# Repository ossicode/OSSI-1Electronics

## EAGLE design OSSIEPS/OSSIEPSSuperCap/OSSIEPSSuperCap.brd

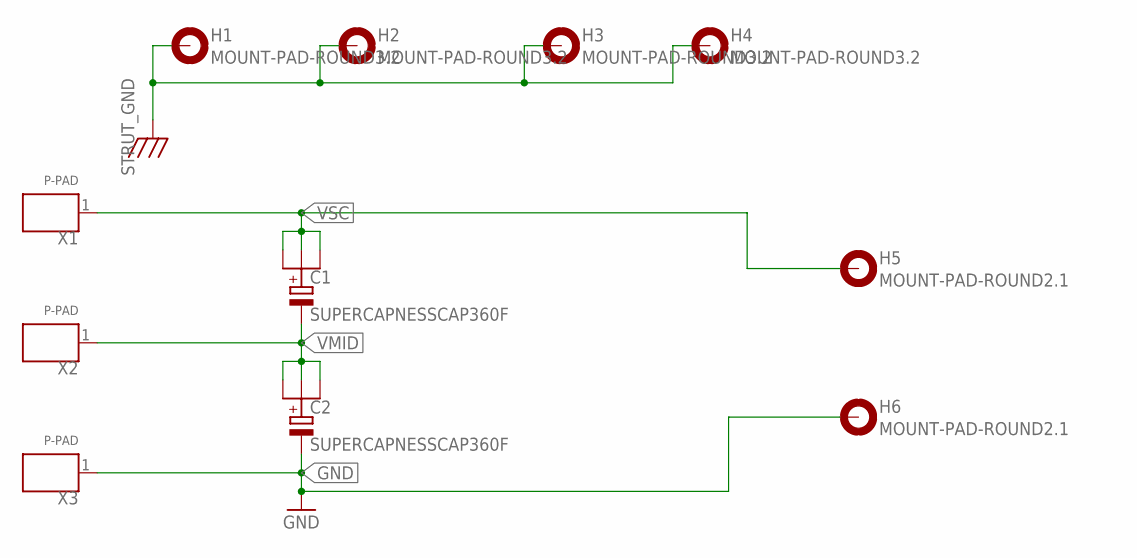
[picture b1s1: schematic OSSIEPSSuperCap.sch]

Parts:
C1, C2: SUPERCAPNESSCAP360F; NESSCAP360F
H1, H2, H3, H4: MOUNT-PAD-ROUND3.2; 3.2-PAD-ROUND
H5, H6: MOUNT-PAD-ROUND2.1; 2.1-PAD-ROUND
X1, X2, X3: P-PAD

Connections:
GND: C2.N, H6.B3,2, X3.1
STRUT_GND: H1.B3,2, H2.B3,2, H3.B3,2, H4.B3,2
VMID: C1.N, C2.P1, C2.P2, C2.P3, X2.1
VSC: C1.P1, C1.P2, C1.P3, H5.B3,2, X1.1

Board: 2 copper layers, 11 parts (0 on the bottom side), 4 nets, no tracks yet.

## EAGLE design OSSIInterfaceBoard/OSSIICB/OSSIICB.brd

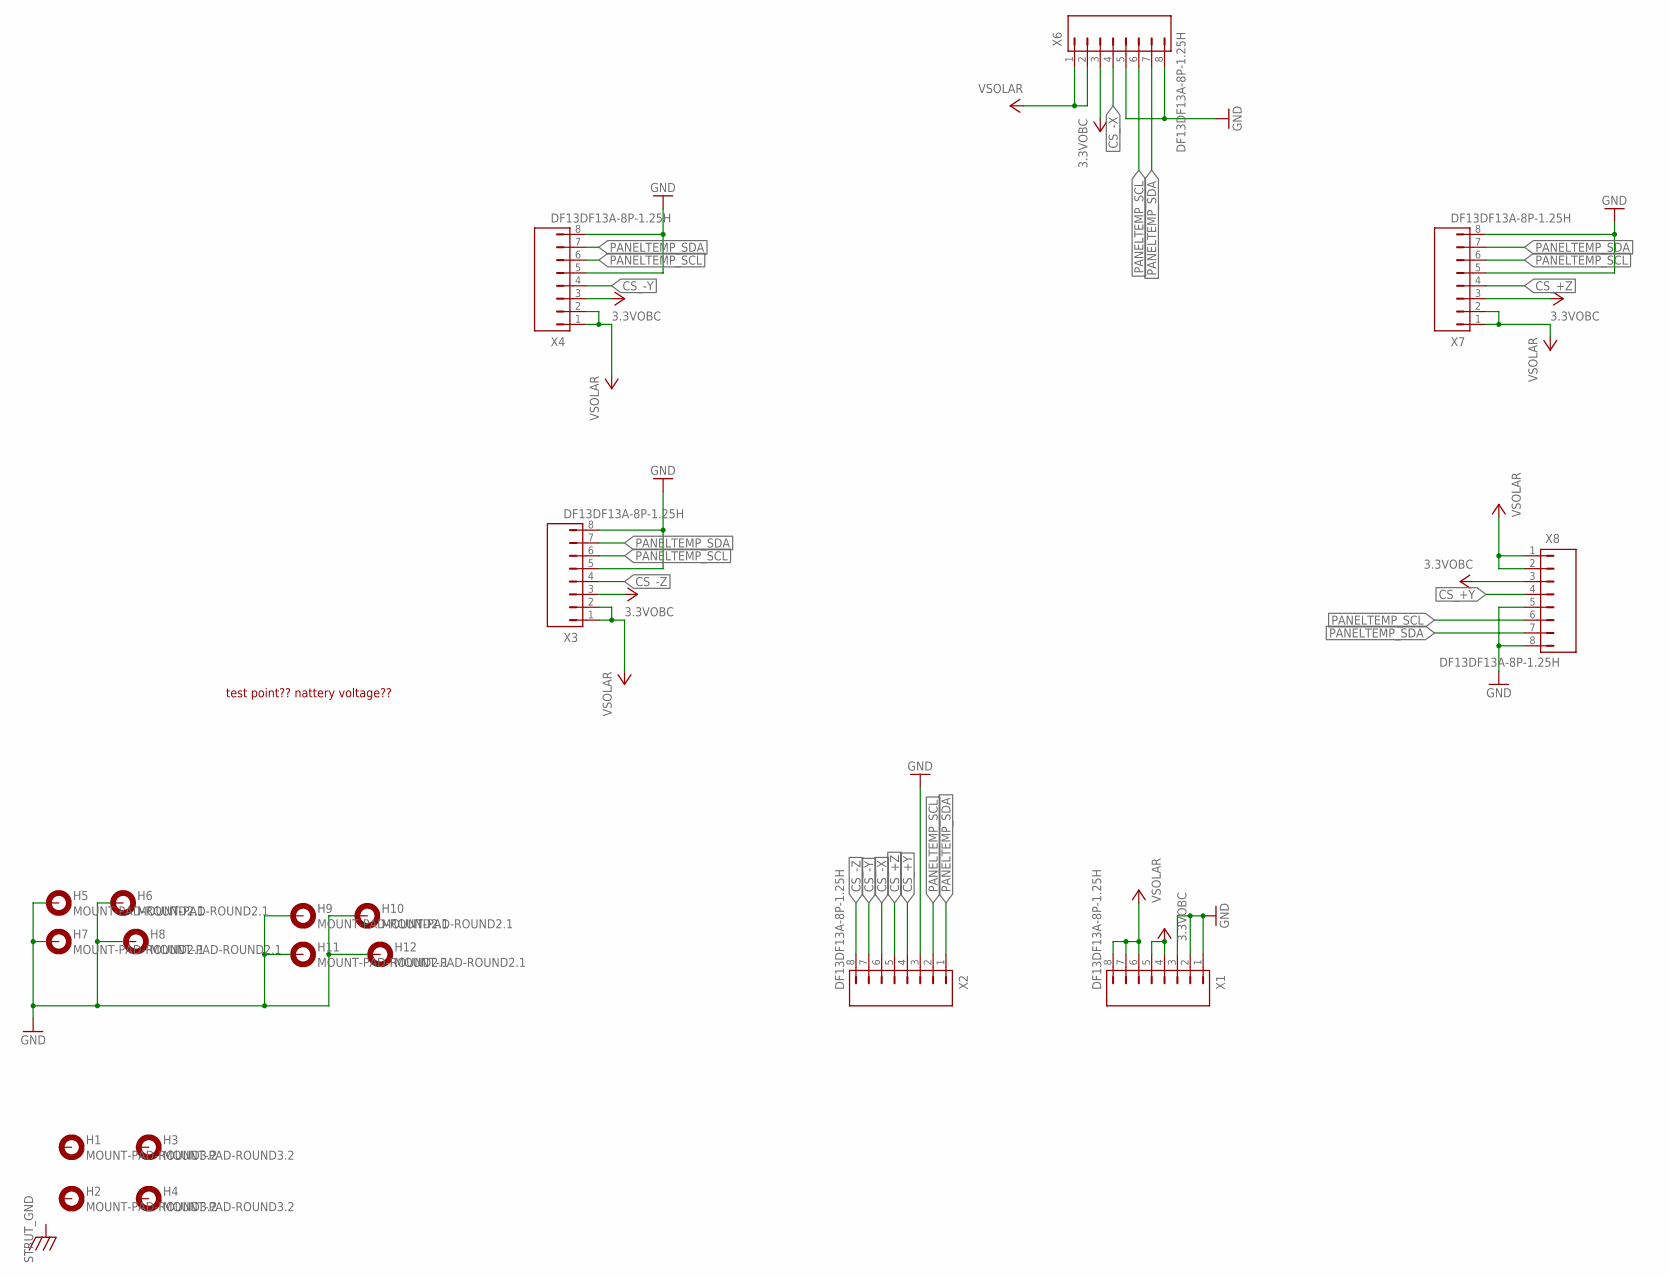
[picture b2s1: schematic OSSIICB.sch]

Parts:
H1, H2, H3, H4: MOUNT-PAD-ROUND3.2; 3.2-PAD-ROUND
H5, H6, H7, H8, H9, H10, H11, H12: MOUNT-PAD-ROUND2.1; 2.1-PAD-ROUND
X1, X2, X3, X4, X6, X7, X8: DF13DF13A-8P-1.25H; DF13A-8P

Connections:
3.3VOBC: X1.4, X1.5, X3.3, X4.3, X6.3, X7.3, X8.3
CS_+Y: X2.4, X8.4
CS_+Z: X2.5, X7.4
CS_-X: X2.6, X6.4
CS_-Y: X2.7, X4.4
CS_-Z: X2.8, X3.4
GND: H5.B3,2, H6.B3,2, H7.B3,2, H8.B3,2, H9.B3,2, H10.B3,2, H11.B3,2, H12.B3,2, X1.1, X1.2, X1.3, X2.3, X3.5, X3.8, X4.5, X4.8, X6.5, X6.8, X7.5, X7.8, X8.5, X8.8
PANELTEMP_SCL: X2.2, X3.6, X4.6, X6.6, X7.6, X8.6
PANELTEMP_SDA: X2.1, X3.7, X4.7, X6.7, X7.7, X8.7
VSOLAR: X1.6, X1.7, X1.8, X3.1, X3.2, X4.1, X4.2, X6.1, X6.2, X7.1, X7.2, X8.1, X8.2

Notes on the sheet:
test point?? nattery voltage??

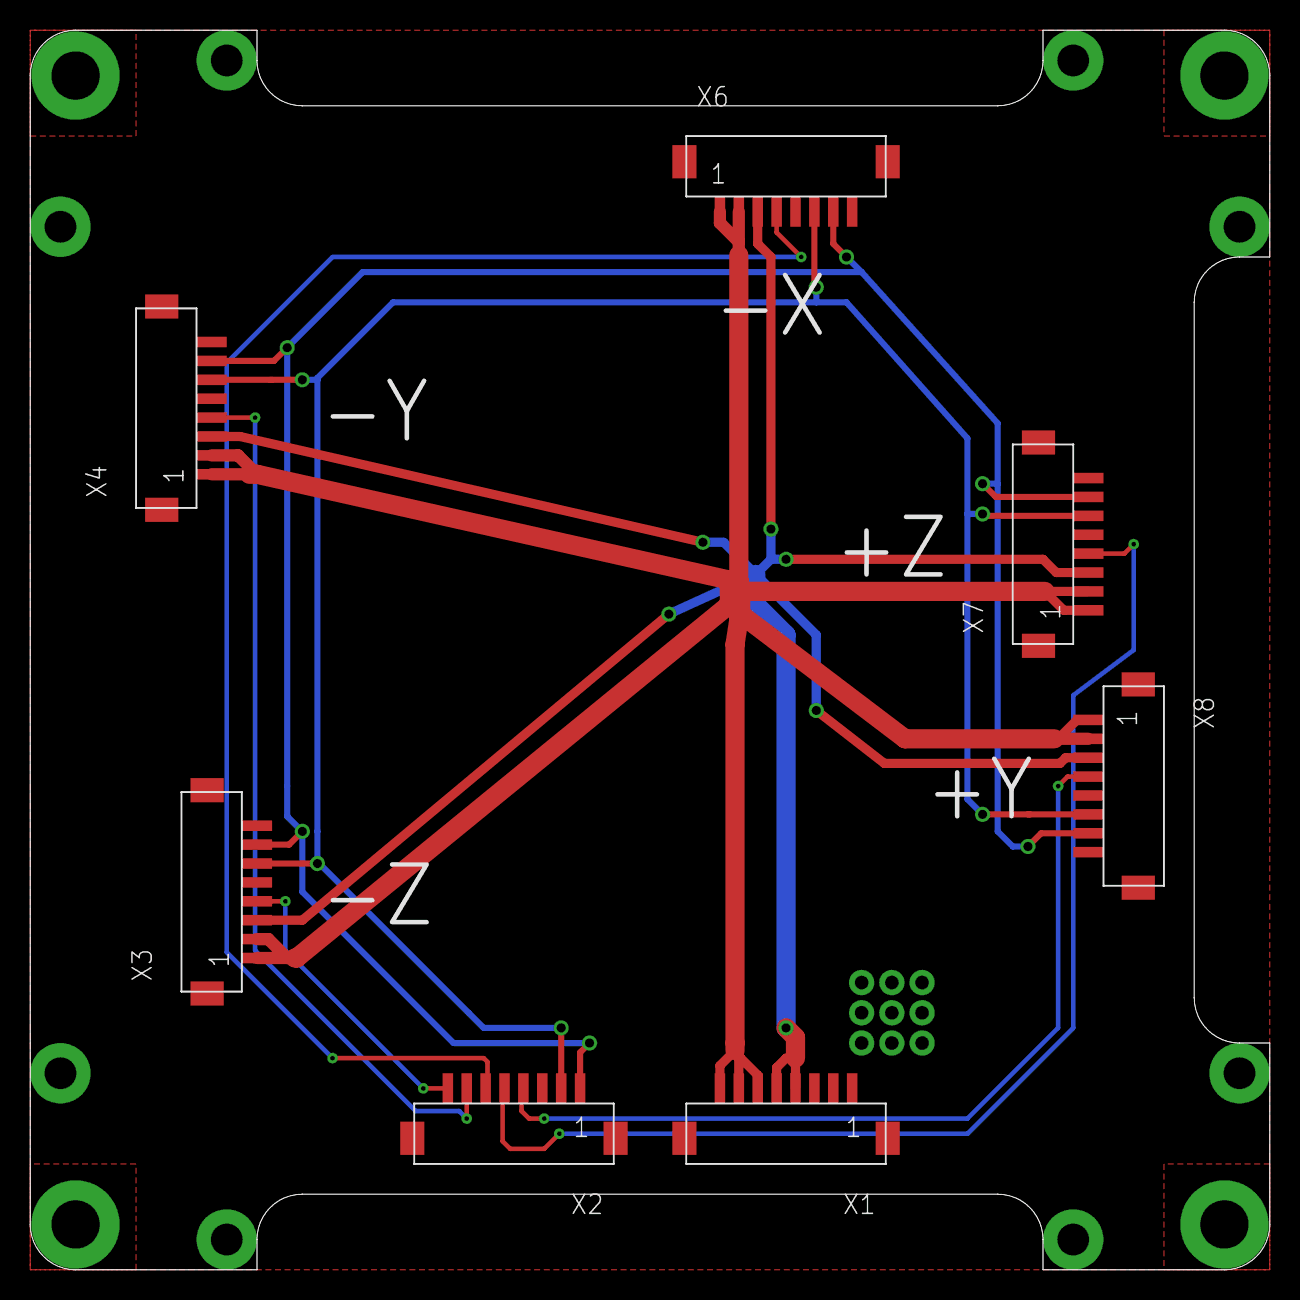
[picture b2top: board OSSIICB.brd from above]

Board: 2 copper layers, 82.0 x 82.0 mm, 19 parts (0 on the bottom side), 10 nets.

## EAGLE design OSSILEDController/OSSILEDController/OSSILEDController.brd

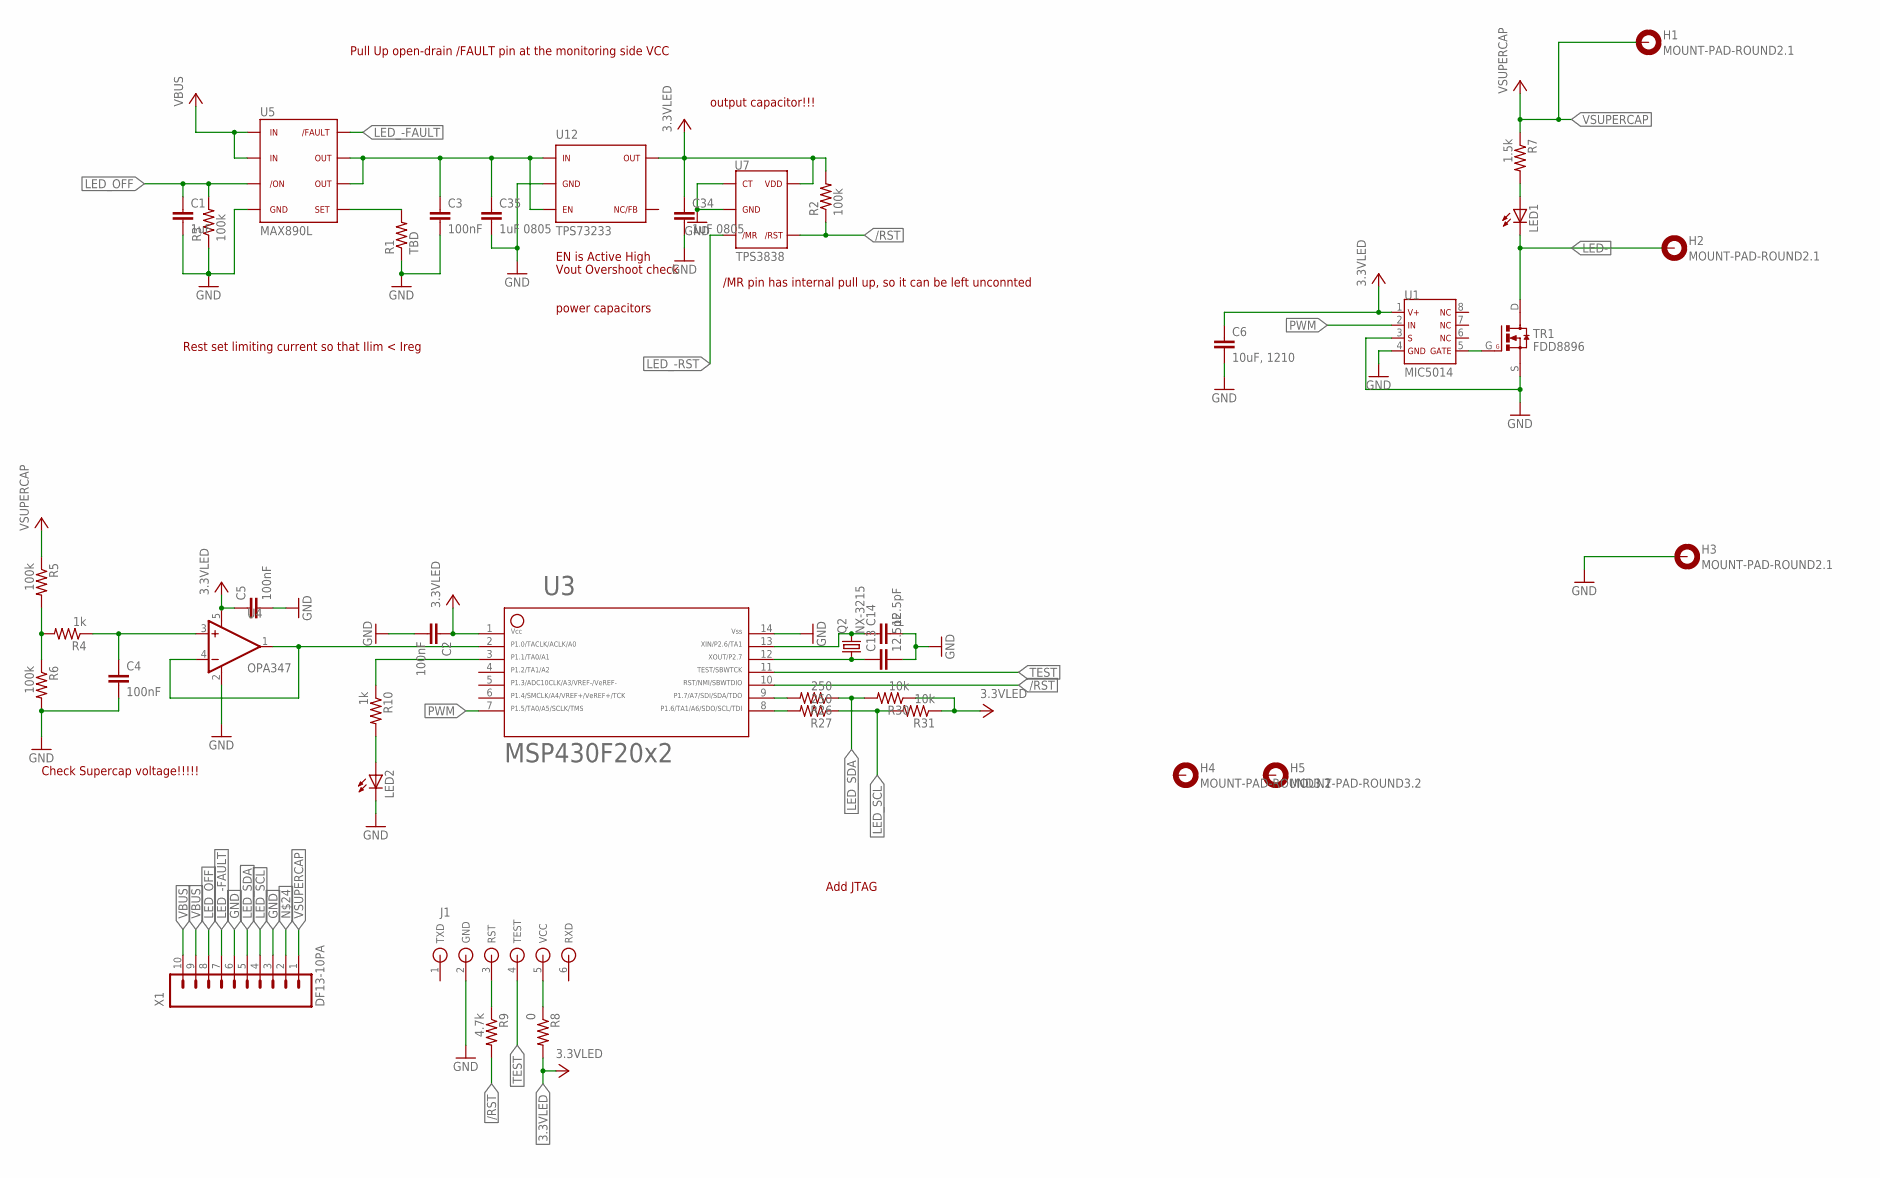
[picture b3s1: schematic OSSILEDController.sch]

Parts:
C1: 1uF; C0603(1608)
C2, C3, C4, C5: 100nF; C0603(1608)
C6: 10uF, 1210; C1210-GCM32
C13, C14: 12.5pF; C0603(1608)
C34, C35: 1uF 0805; C0805(2012)
H1, H2, H3: MOUNT-PAD-ROUND2.1; 2.1-PAD-ROUND
H4, H5: MOUNT-PAD-ROUND3.2; 3.2-PAD-ROUND
J1: JTAG-SBW-6; SMD-PAD-6
LED1, LED2: LEDCHIPLED_0603; CHIPLED_0603
Q2: NX-3215
R1: TBD; R0603(1608)
R2, R3, R5, R6: 100k; R0603(1608)
R4, R10: 1k; R0603(1608)
R7: 1.5k; R0603(1608)
R8: 0; R0603(1608)
R9: 4.7k; R0603(1608)
R26, R27: 250; R0603(1608)
R30, R31: 10k; R0603(1608)
TR1: FDD8896; TO252
U1: MIC5014; SO8
U3: MSP430F2012; PW14
U4: OPA347; SOT23-5DBV
U5: MAX890L; SO8
U7: TPS3838; SOT23-5DBV
U12: TPS73233; SOT23-5DBV
X1: DF13-10PA; DF13A-10P

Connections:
3.3VLED: C2.1, C5.1, C6.P$1 (1), C34.1, R2.2, R8.2, R30.1, R31.1, U1.1, U3.1, U4.5 (V+), U7.5, U12.5
/RST: R2.1, R9.2, U3.10, U7.4
GND: C1.2, C2.2, C3.2, C4.2, C5.2, C6.P$2 (2), C13.2, C14.2, C34.2, C35.2, H3.B3,2, J1.2 (GND), LED2.C, R1.1, R3.1, R6.2, TR1.S, U1.3, U1.4, U3.14, U4.2 (V-), U5.4, U7.1, U7.2, U12.2, X1.3, X1.6
LED-: H2.B3,2, LED1.C, TR1.D
LED_-FAULT: U5.8, X1.7
LED_-RST: U7.3
LED_OFF: C1.1, R3.2, U5.3, X1.8
LED_SCL: R27.1, R31.2, X1.4
LED_SDA: R26.1, R30.2, X1.5
unnamed: TR1.G, U1.5
unnamed: J1.3 (RST), R9.1
unnamed: C4.1, R4.1, U4.3 (+IN)
unnamed: R26.2, U3.9
unnamed: C3.1, C35.1, U5.6, U5.7, U12.1, U12.3
unnamed: C13.1, Q2.1, U3.12
unnamed: C14.1, Q2.2, U3.13
unnamed: R27.2, U3.8
unnamed: R1.2, U5.5
unnamed: R4.2, R5.2, R6.1
unnamed: LED1.A, R7.2
unnamed: LED2.A, R10.2
unnamed: U3.2, U4.1 (OUT), U4.4 (-IN)
unnamed: J1.5 (VCC), R8.1
unnamed: R10.1, U3.3
PWM: U1.2, U3.7
TEST: J1.4 (TEST), U3.11
VBUS: U5.1, U5.2, X1.9, X1.10
VSUPERCAP: H1.B3,2, R5.1, R7.1, X1.1

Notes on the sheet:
Rest set limiting current so that Ilim < Ireg
Pull Up open-drain /FAULT pin at the monitoring side VCC
EN is Active High
/MR pin has internal pull up, so it can be left unconnted
Vout Overshoot check
power capacitors
output capacitor!!!
Check Supercap voltage!!!!!
Add JTAG

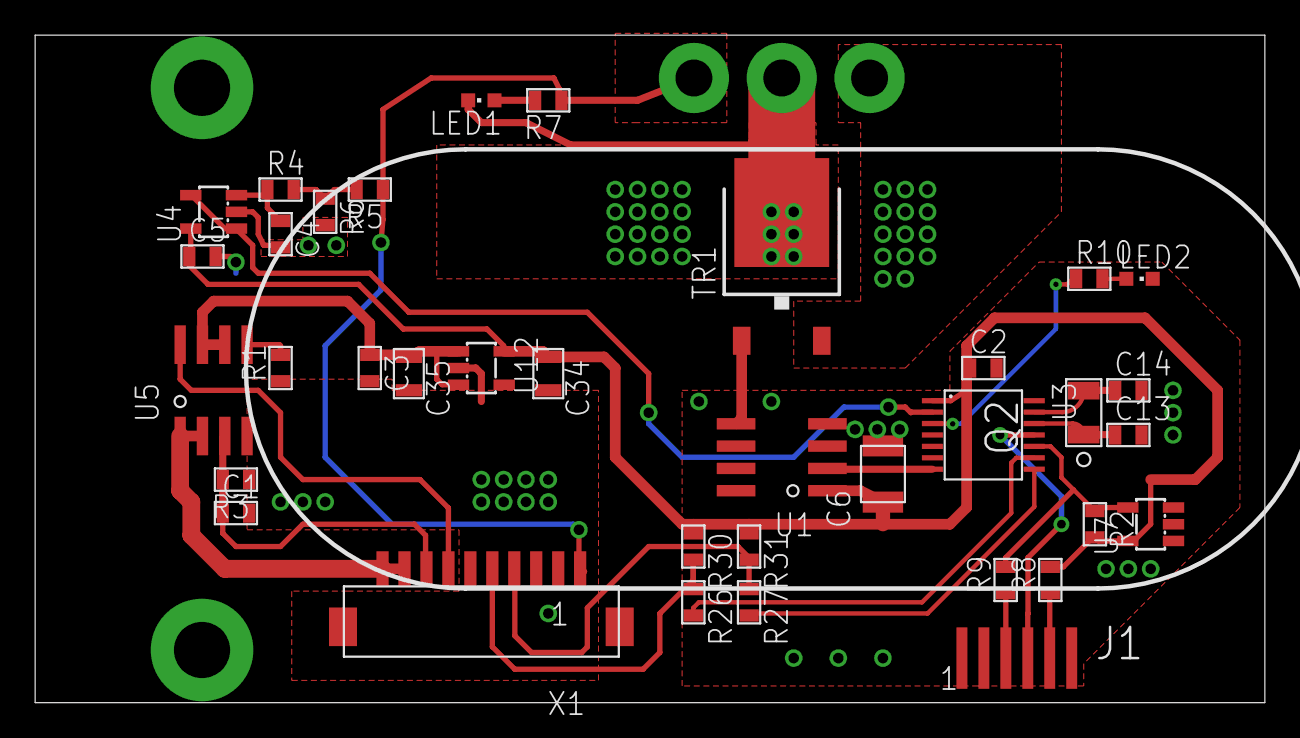
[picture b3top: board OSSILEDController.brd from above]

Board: 2 copper layers, 70.0 x 38.0 mm, 41 parts (0 on the bottom side), 27 nets.

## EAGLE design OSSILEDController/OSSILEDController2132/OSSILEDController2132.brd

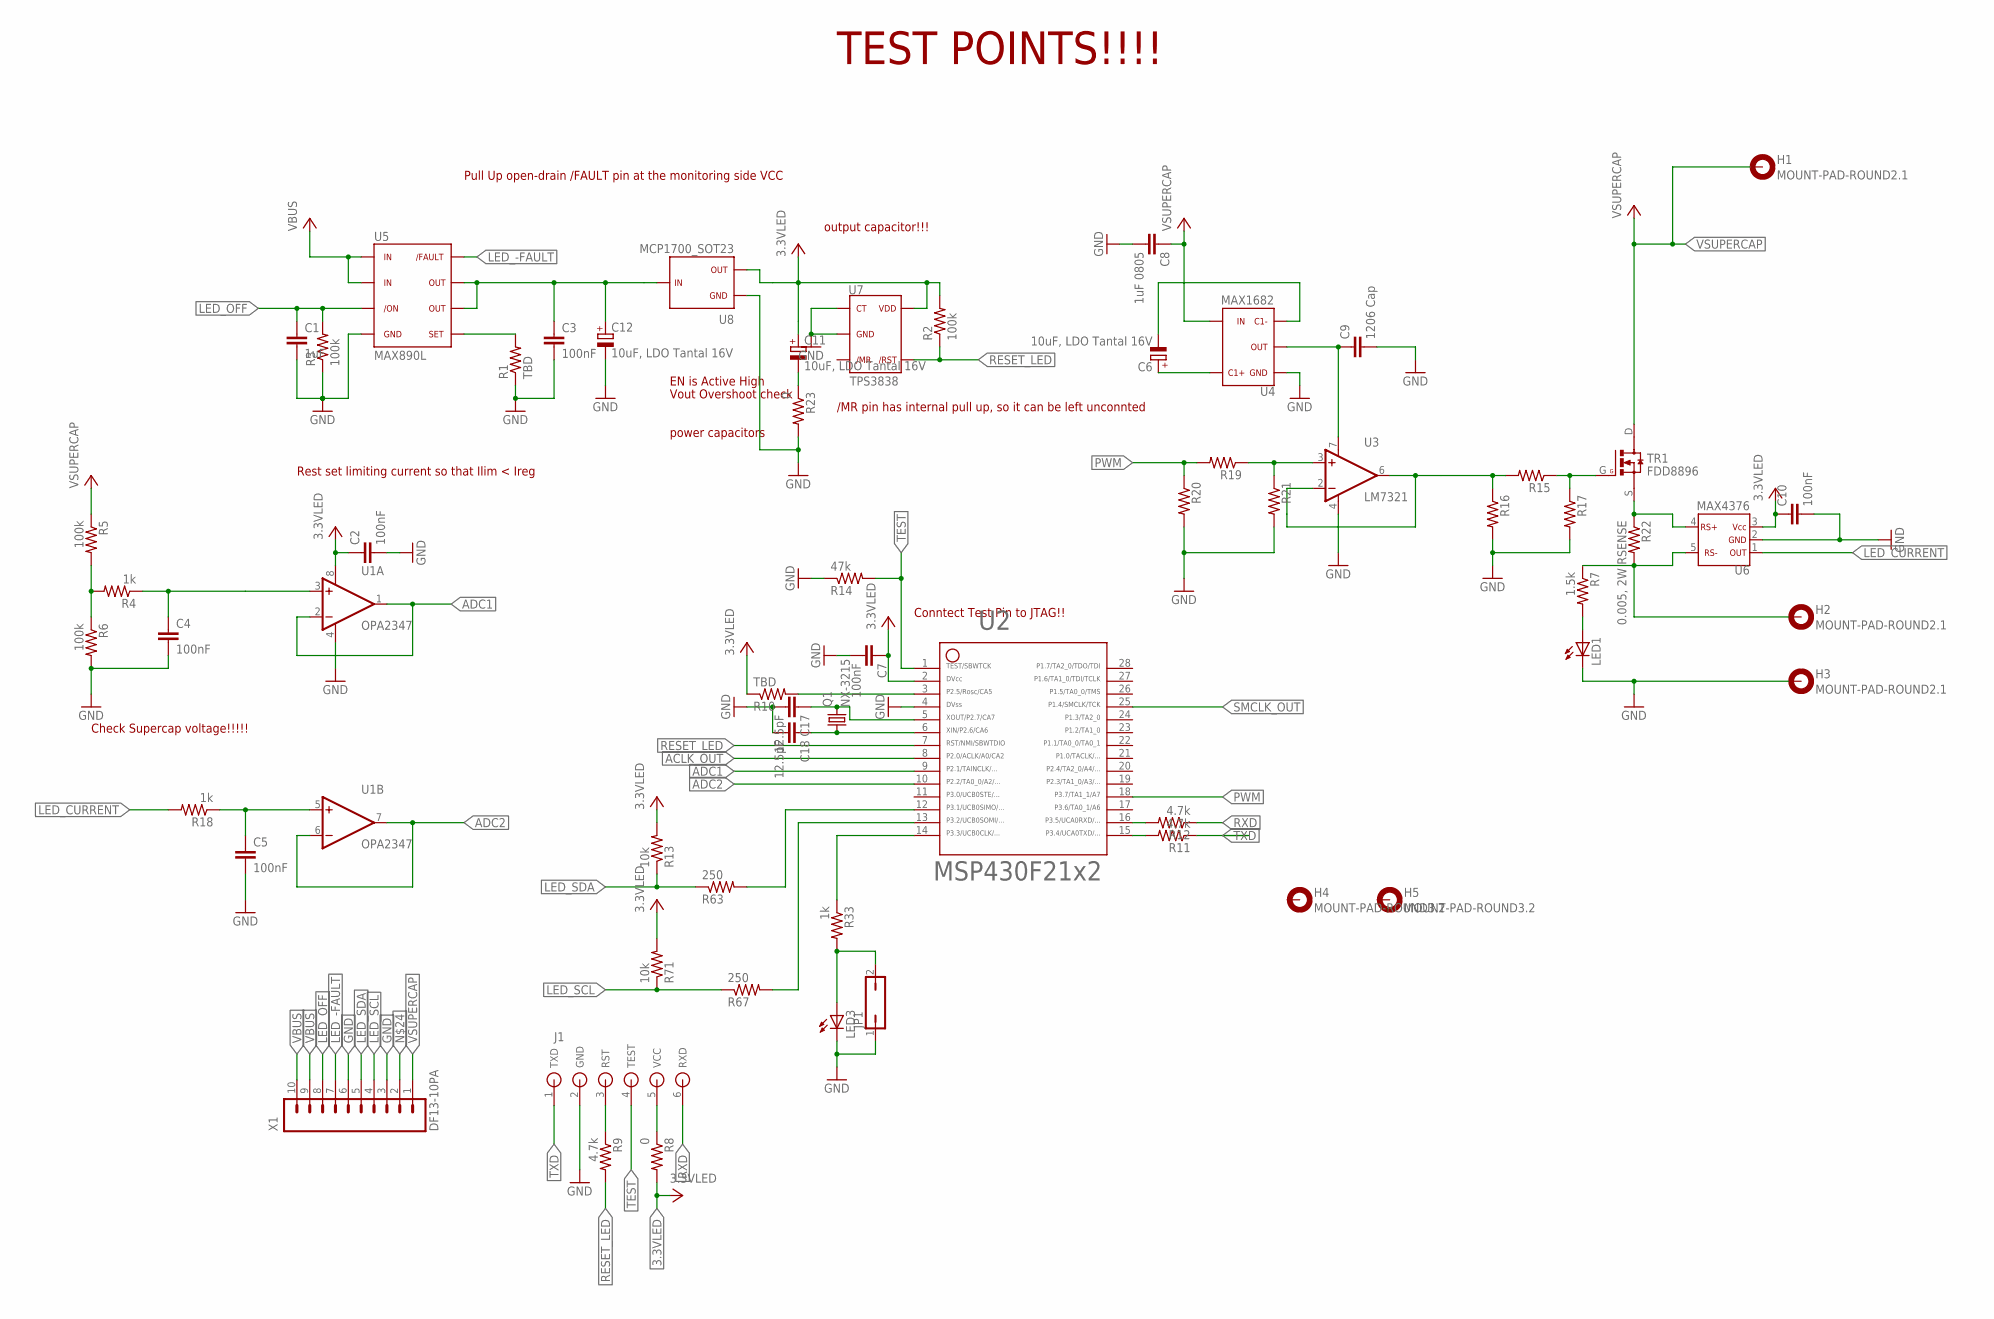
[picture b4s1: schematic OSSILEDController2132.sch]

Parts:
C1: 1uF; C0603(1608)
C2, C3, C4, C5, C7, C10: 100nF; C0603(1608)
C6, C11, C12: 10uF, LDO Tantal 16V; C1206(3216)-A
C8: 1uF 0805; C0805(2012)
C9: 1206 Cap; C1206-GCM31
C17, C18: 12.5pF; C0603(1608)
H1, H2, H3: MOUNT-PAD-ROUND2.1; 2.1-PAD-ROUND
H4, H5: MOUNT-PAD-ROUND3.2; 3.2-PAD-ROUND
J1: JTAG-SBW-6; SMD-PAD-6
JP1: JP1Q; JP1
LED1: LEDCHIPLED_0603; CHIPLED_0603
LED3: LED0603; LED-0603
Q1: NX-3215
R1, R10: TBD; R0603(1608)
R2, R3, R5, R6: 100k; R0603(1608)
R4, R18, R33: 1k; R0603(1608)
R7: 1.5k; R0603(1608)
R8, R23: 0; R0603(1608)
R9, R11, R12: 4.7k; R0603(1608)
R13, R71: 10k; R0603(1608)
R14: 47k; R0603(1608)
R15, R16, R17, R19, R20, R21: R0603(1608)
R22: 0.005, 2W RSENSE; R4527(12070)
R63, R67: 250; R0603(1608)
TR1: FDD8896; TO252
U1: OPA2347; SOT23-8DCN
U2: MSP430F2132; PW28
U3: LM7321; SO8
U4: MAX1682; SOT23-5DBV
U5: MAX890L; SO8
U6: MAX4376; SOT23-5DBV
U7: TPS3838; SOT23-5DBV
U8: MCP1700_SOT23; SOT23
X1: DF13-10PA; DF13A-10P

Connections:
3.3VLED: C2.1, C7.1, C10.1, C11.1 (+), R2.2, R8.2, R10.1, R13.2, R71.2, U1.8 (V+), U2.2, U6.3, U7.5, U8.2
ACLK_OUT: U2.8
ADC1: U1.1 (OUT), U1.2 (-IN), U2.9
ADC2: U1.6 (-IN), U1.7 (OUT), U2.10
GND: C1.2, C2.2, C3.2, C4.2, C5.2, C7.2, C8.2, C9.P$2 (2), C10.2, C12.2 (-), C17.2, C18.2, H3.B3,2, J1.2 (GND), JP1.1, LED1.C, LED3.C, R1.1, R3.1, R6.2, R14.1, R16.2, R17.2, R20.2, R21.2, R23.2, U1.4 (V-), U2.4, U3.4 (V-), U4.1, U5.4, U6.2, U7.1, U7.2, U8.1, X1.3, X1.6
LED_-FAULT: U5.8, X1.7
LED_CURRENT: R18.2, U6.1
LED_OFF: C1.1, R3.2, U5.3, X1.8
LED_SCL: R67.1, R71.1, X1.4
LED_SDA: R13.1, R63.1, X1.5
unnamed: R10.2, U2.3
unnamed: J1.3 (RST), R9.1
unnamed: C4.1, R4.1, U1.3 (+IN)
unnamed: R15.1, R17.1, TR1.G
unnamed: C3.1, C12.1 (+), U5.6, U5.7, U8.3
unnamed: R19.1, R21.1, U3.3 (+IN)
unnamed: C5.1, R18.1, U1.5 (+IN)
unnamed: H2.B3,2, R7.1, R22.P$2 (2), U6.5
unnamed: R1.2, U5.5
unnamed: R4.2, R5.2, R6.1
unnamed: C11.2 (-), R23.1
unnamed: C9.P$1 (1), U3.7 (V+), U4.2
unnamed: R15.2, R16.1, U3.2 (-IN), U3.6 (OUT)
unnamed: J1.5 (VCC), R8.1
unnamed: R22.P$1 (1), TR1.S, U6.4
unnamed: C17.1, Q1.2, U2.5
unnamed: C18.1, Q1.1, U2.6
unnamed: JP1.2, LED3.A, R33.2
unnamed: R63.2, U2.12
unnamed: R67.2, U2.13
unnamed: R33.1, U2.14
unnamed: C6.2 (-), U4.3
unnamed: C6.1 (+), U4.5
unnamed: R12.2, U2.16
unnamed: LED1.A, R7.2
unnamed: R11.2, U2.15
PWM: R19.2, R20.1, U2.18
RESET_LED: R2.1, R9.2, U2.7, U7.4
RXD: J1.6 (RXD), R12.1
SMCLK_OUT: U2.25
TEST: J1.4 (TEST), R14.2, U2.1
TXD: J1.1 (TXD), R11.1
VBUS: U5.1, U5.2, X1.9, X1.10
VSUPERCAP: C8.1, H1.B3,2, R5.1, TR1.D, U4.4, X1.1

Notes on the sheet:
Rest set limiting current so that Ilim < Ireg
Pull Up open-drain /FAULT pin at the monitoring side VCC
EN is Active High
/MR pin has internal pull up, so it can be left unconnted
Vout Overshoot check
power capacitors
output capacitor!!!
Conntect Test Pin to JTAG!!
Check Supercap voltage!!!!!
TEST POINTS!!!!

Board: 2 copper layers, 61 parts (2 on the bottom side), 42 nets, no tracks yet.

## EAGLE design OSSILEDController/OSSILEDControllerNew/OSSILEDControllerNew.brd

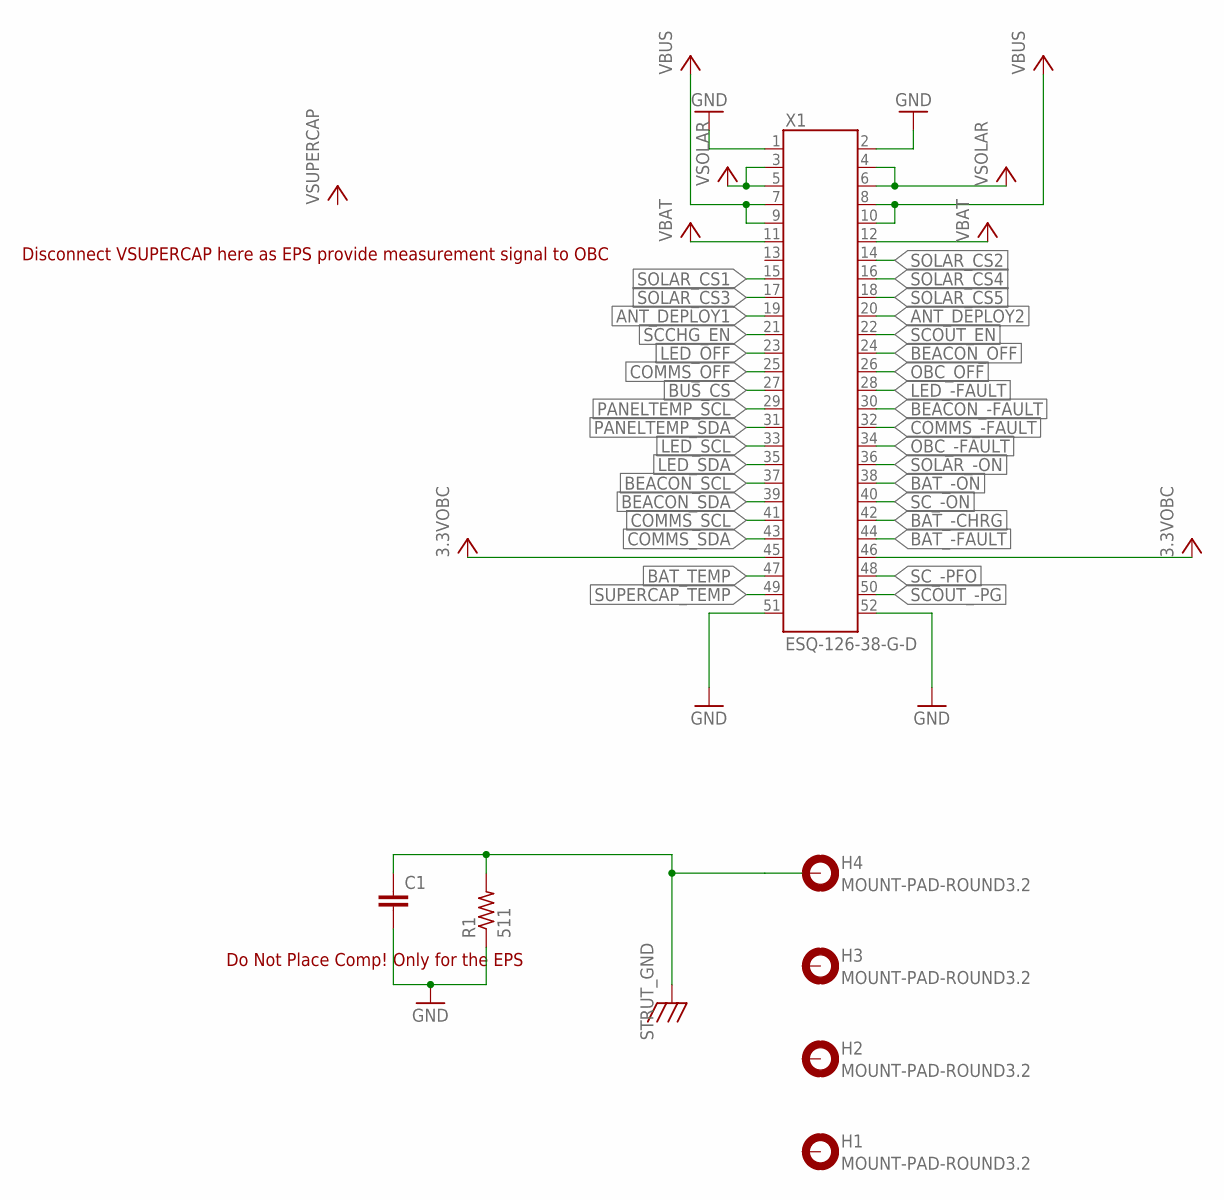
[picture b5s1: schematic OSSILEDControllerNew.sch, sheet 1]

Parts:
C1: C0805(2012)
H1, H2, H3, H4: MOUNT-PAD-ROUND3.2; 3.2-PAD-ROUND
R1: 511; WSL1206
X1: ESQ-126-38-G-D; ESQ-126-XX-X-D

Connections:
3.3VOBC: X1.45, X1.46
ANT_DEPLOY1: X1.19
ANT_DEPLOY2: X1.20
BAT_-CHRG: X1.42
BAT_-FAULT: X1.44
BAT_-ON: X1.38
BAT_TEMP: X1.47
BEACON_-FAULT: X1.30
BEACON_OFF: X1.24
BEACON_SCL: X1.37
BEACON_SDA: X1.39
BUS_CS: X1.27
COMMS_-FAULT: X1.32
COMMS_OFF: X1.25
COMMS_SCL: X1.41
COMMS_SDA: X1.43
GND: C1.2, R1.P$1 (1), X1.1, X1.2, X1.51, X1.52; also elsewhere on the board
LED_-FAULT: X1.28; also elsewhere on the board
LED_OFF: X1.23; also elsewhere on the board
LED_SCL: X1.33; also elsewhere on the board
LED_SDA: X1.35; also elsewhere on the board
OBC_-FAULT: X1.34
OBC_OFF: X1.26
PANELTEMP_SCL: X1.29
PANELTEMP_SDA: X1.31
SCCHG_EN: X1.21
SCOUT_-PG: X1.50
SCOUT_EN: X1.22
SC_-ON: X1.40
SC_-PFO: X1.48
SOLAR_-ON: X1.36
SOLAR_CS1: X1.15
SOLAR_CS2: X1.14
SOLAR_CS3: X1.17
SOLAR_CS4: X1.16
SOLAR_CS5: X1.18
STRUT_GND: C1.1, H4.B3,2, R1.P$2 (2)
SUPERCAP_TEMP: X1.49
VBAT: X1.11, X1.12
VBUS: X1.7, X1.8, X1.9, X1.10; also elsewhere on the board
VSOLAR: X1.3, X1.4, X1.5, X1.6

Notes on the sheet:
Disconnect VSUPERCAP here as EPS provide measurement signal to OBC
Do Not Place Comp! Only for the EPS

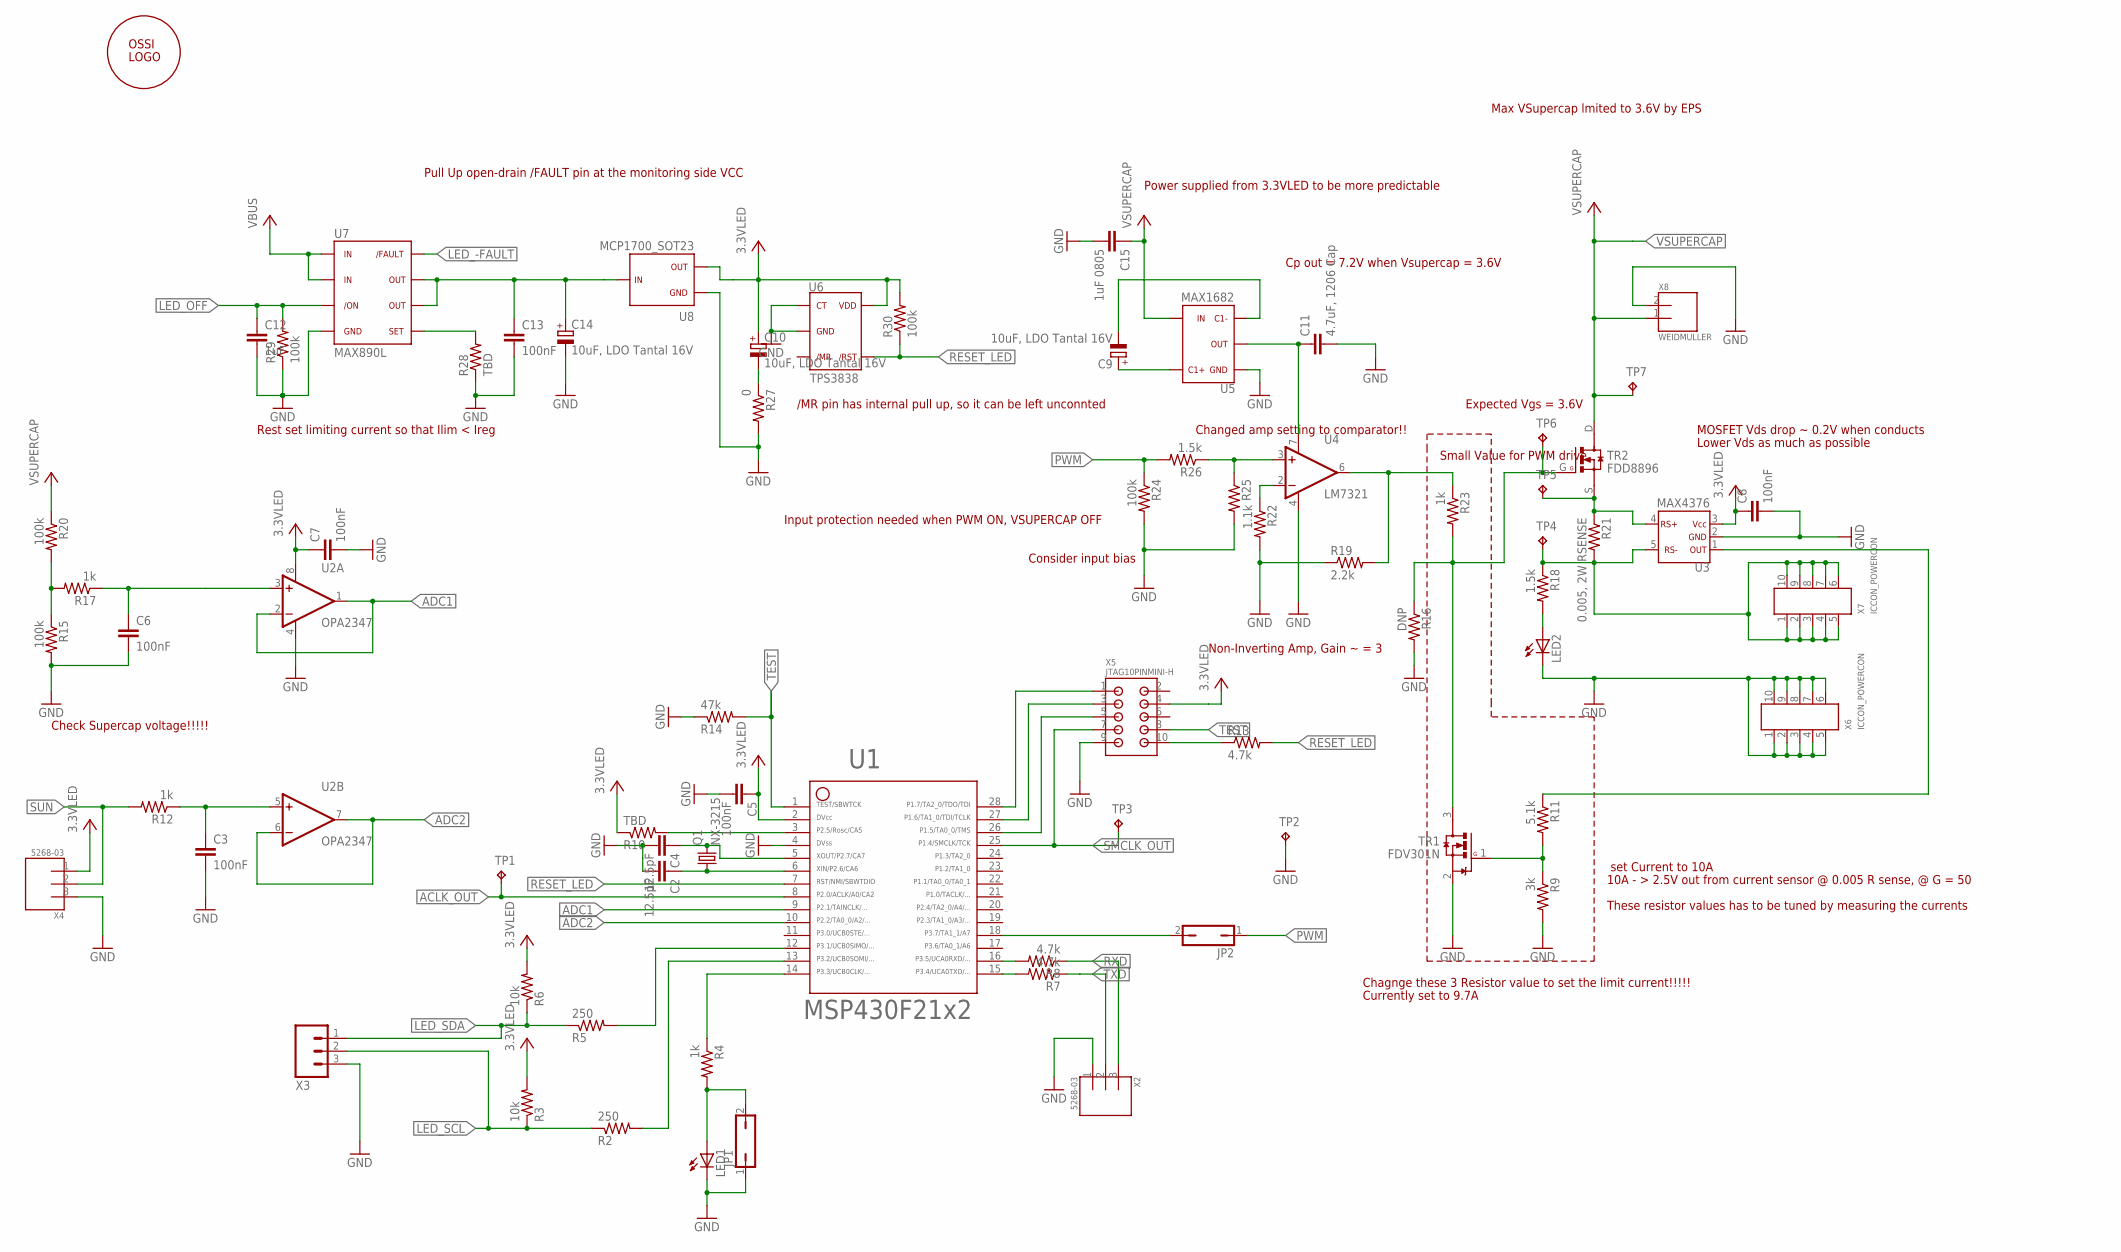
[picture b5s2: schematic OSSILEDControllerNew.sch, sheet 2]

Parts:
C2, C4: 12.5pF; C0603(1608)
C3, C5, C6, C7, C8, C13: 100nF; C0603(1608)
C9, C10, C14: 10uF, LDO Tantal 16V; C1206(3216)-A
C11: 4.7uF, 1206 Cap; C1206-GCM31
C12: 1uF; C0603(1608)
C15: 1uF 0805; C0805(2012)
JP1, JP2: JP1Q; JP1
LED1: LED0603; LED-0603
LED2: LEDCHIPLED_0603; CHIPLED_0603
Q1: NX-3215
R2, R5: 250; R0603(1608)
R3, R6: 10k; R0603(1608)
R4, R12, R17, R23: 1k; R0603(1608)
R7, R8, R13: 4.7k; R0603(1608)
R9: 3k; R0603(1608)
R10, R28: TBD; R0603(1608)
R11: 5.1k; R0603(1608)
R14: 47k; R0603(1608)
R15, R20, R24, R29, R30: 100k; R0603(1608)
R16: DNP; R0603(1608)
R18, R26: 1.5k; R0603(1608)
R19: 2.2k; R0603(1608)
R21: 0.005, 2W RSENSE; R4527(12070)
R22: 1.1k; R0603(1608)
R25: R0603(1608)
R27: 0; R0603(1608)
TP1, TP2, TP3, TP4, TP5, TP6, TP7: TP; TP-13
TR1: FDV301N; SOT23
TR2: FDD8896; TO252
U1: MSP430F2132; PW28
U2: OPA2347; SOT23-8DCN
U3: MAX4376; SOT23-5DBV
U4: LM7321; SO8
U5: MAX1682; SOT23-5DBV
U6: TPS3838; SOT23-5DBV
U7: MAX890L; SO8
U8: MCP1700_SOT23; SOT23
U$: OSSILOGORECT; OSSILOGORECT1005
X2, X4: 5268-03
X3: M03PTH; 1X03
X5: JTAG10PINMINI-H; M50-3200545
X6, X7: ICCON_POWERCON; ICCON6643220-1
X8: WEIDMULLER; WEIDMULLER1760490000

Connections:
3.3VLED: C5.1, C7.1, C8.1, C10.1 (+), R3.2, R6.2, R10.1, R30.2, U1.2, U2.8 (V+), U3.3, U6.5, U8.2, X4.1, X5.4
ACLK_OUT: TP1.TP, U1.8
ADC1: U1.9, U2.1 (OUT), U2.2 (-IN)
ADC2: U1.10, U2.6 (-IN), U2.7 (OUT)
GND: C2.2, C3.2, C4.2, C5.2, C6.2, C7.2, C8.2, C11.P$2 (2), C12.2, C13.2, C14.2 (-), C15.2, JP1.1, LED1.C, LED2.C, R9.2, R14.1, R15.2, R16.2, R19.1, R22.2, R24.2, R25.2, R27.2, R28.1, R29.1, TP2.TP, TR1.2 (S), U1.4, U2.4 (V-), U3.2, U4.4 (V-), U5.1, U6.1, U6.2, U7.4, U8.1, X2.1, X3.3, X4.3, X5.9, X6.1, X6.2, X6.3, X6.4, X6.5, X6.6, X6.7, X6.8, X6.9, X6.10, X8.2; also elsewhere on the board
LED_-FAULT: U7.8; also elsewhere on the board
LED_OFF: C12.1, R29.2, U7.3; also elsewhere on the board
LED_SCL: R2.1, R3.1, X3.2; also elsewhere on the board
LED_SDA: R5.1, R6.1, X3.1; also elsewhere on the board
unnamed: U1.28, X5.1
unnamed: R10.2, U1.3
unnamed: C13.1, C14.1 (+), U7.6, U7.7, U8.3
unnamed: R16.1, R23.2, TP6.TP, TR1.3 (D), TR2.G
unnamed: C6.1, R17.1, U2.3 (+IN)
unnamed: C3.1, R12.1, U2.5 (+IN)
unnamed: R25.1, R26.1, U4.3 (+IN)
unnamed: R28.2, U7.5
unnamed: R15.1, R17.2, R20.2
unnamed: R18.1, R21.P$2 (2), TP4.TP, U3.5, X7.1, X7.2, X7.3, X7.4, X7.5, X7.6, X7.7, X7.8, X7.9, X7.10
unnamed: C11.P$1 (1), U4.7 (V+), U5.2
unnamed: R19.2, R23.1, U4.6 (OUT)
unnamed: U1.27, X5.3
unnamed: R21.P$1 (1), TP5.TP, TR2.S, U3.4
unnamed: C10.2 (-), R27.1
unnamed: R22.1, U4.2 (-IN)
unnamed: C4.1, Q1.2, U1.5
unnamed: C2.1, Q1.1, U1.6
unnamed: JP1.2, LED1.A, R4.2
unnamed: R5.2, U1.12
unnamed: R2.2, U1.13
unnamed: R11.1, U3.1
unnamed: R4.1, U1.14
unnamed: C9.2 (-), U5.3
unnamed: C9.1 (+), U5.5
unnamed: R8.2, U1.16
unnamed: LED2.A, R18.2
unnamed: R9.1, R11.2, TR1.1 (G)
unnamed: U1.26, X5.5
unnamed: R13.1, X5.10
unnamed: JP2.2, U1.18
unnamed: R7.2, U1.15
PWM: JP2.1, R24.1, R26.2
RESET_LED: R13.2, R30.1, U1.7, U6.4
RXD: R8.1, X2.3
SMCLK_OUT: TP3.TP, U1.25, X5.7
SUN: R12.2, X4.2
TEST: R14.2, U1.1, X5.8
TXD: R7.1, X2.2
VBUS: U7.1, U7.2; also elsewhere on the board
VSUPERCAP: C15.1, R20.1, TP7.TP, TR2.D, U5.4, X8.1

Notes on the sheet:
Rest set limiting current so that Ilim < Ireg
Pull Up open-drain /FAULT pin at the monitoring side VCC
/MR pin has internal pull up, so it can be left unconnted
Check Supercap voltage!!!!!
Non-Inverting Amp, Gain ~ = 3
set Current to 10A
10A - > 2.5V out from current sensor @ 0.005 R sense, @ G = 50
Chagnge these 3 Resistor value to set the limit current!!!!!
Expected Vgs = 3.6V
Max VSupercap lmited to 3.6V by EPS
Cp out = 7.2V when Vsupercap = 3.6V
Input protection needed when PWM ON, VSUPERCAP OFF
Currently set to 9.7A
Changed amp setting to comparator!!
Power supplied from 3.3VLED to be more predictable
These resistor values has to be tuned by measuring the currents
Small Value for PWM drive
MOSFET Vds drop ~ 0.2V when conducts
Lower Vds as much as possible
Consider input bias

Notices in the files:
parts and their libraries:
SparkFun: Licensing: CC v3.0 Share-Alike You are welcome to use this library for commercial purposes.
